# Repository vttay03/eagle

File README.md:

eagle
=====

misc. eagle pcb projects

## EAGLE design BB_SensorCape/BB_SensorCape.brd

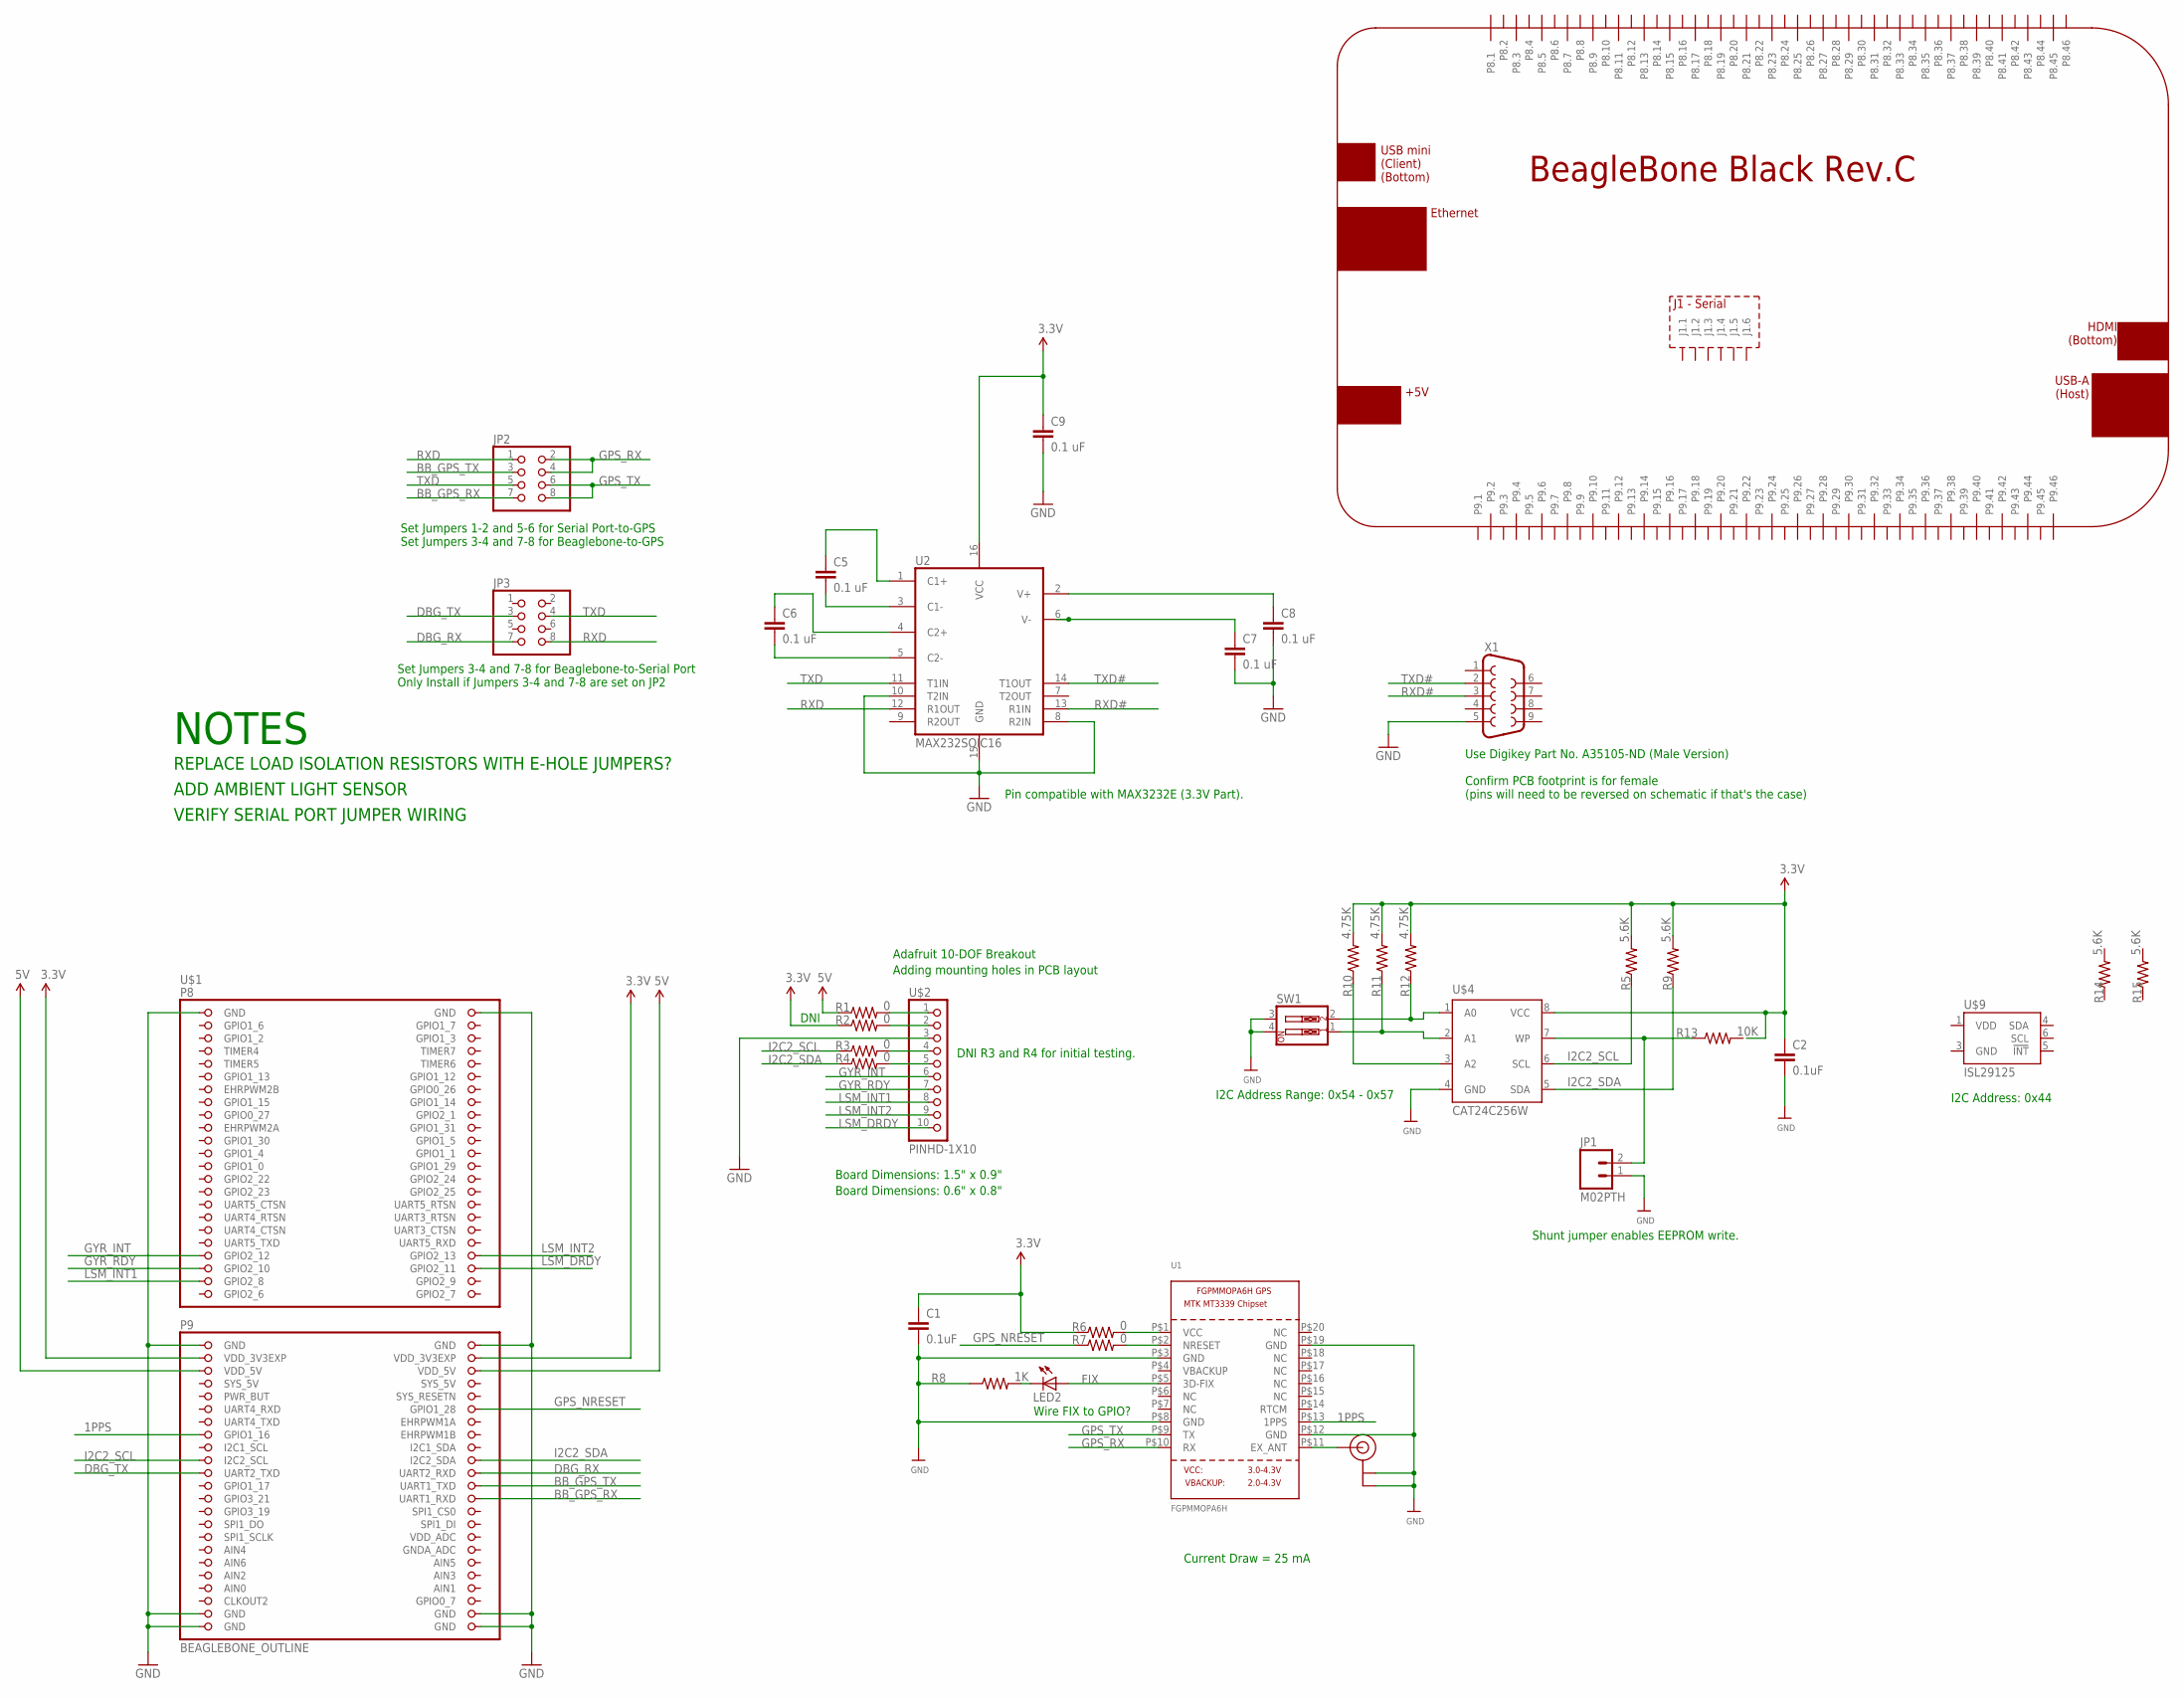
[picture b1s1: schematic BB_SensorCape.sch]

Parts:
C1, C2: 0.1uF; 0603-CAP
C5, C6, C7, C8, C9: 0.1 uF; 0805
JP1: M02PTH; 1X02
JP2, JP3: PINHD-2X4; 2X04
LED2: LEDCHIPLED_0805; CHIPLED_0805
PCB1: BEAGLEBONE_BLACK
R1, R2, R3, R4, R6, R7: 0; R0603
R5, R9, R14, R15: 5.6K; R0603
R8: 1K; R0603
R10, R11, R12: 4.75K; R0603
R13: 10K; R0603
SW1: SW_DIP-2-SMT-HALFSIZE; DIPSWITCH-02-50MIL
U1: FGPMMOPA6H
U2: MAX232SOIC16; SO016
U$1: BEAGLEBONE_OUTLINE; BEAGLEBONE_SHIELD
U$2: PINHD-1X10; 1X10-BIG
U$4: CAT24C256W; SO08
U$9: ISL29125; ODFN-LD-6
U$20: U.FL
X1: DB9MALE; DB9_MALE

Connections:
1PPS: PCB1.P9.15, U1.P$13 (1PPS), U$1.61 (GPIO1_16)
3.3V: C1.1, C2.1, C9.1, PCB1.P9.3, PCB1.P9.4, R2.1, R5.2, R6.1, R9.2, R10.2, R11.2, R12.2, R14.2, R15.2, U2.16 (VCC), U$1.49 (VDD_3V3EXP), U$1.50 (VDD_3V3EXP), U$4.8 (VCC); also elsewhere on the board
5V: PCB1.P9.5, PCB1.P9.6, R1.1, U$1.51 (VDD_5V), U$1.52 (VDD_5V)
BB_GPS_RX: JP2.7, PCB1.P9.26, U$1.72 (UART1_RXD)
BB_GPS_TX: JP2.3, PCB1.P9.24, U$1.70 (UART1_TXD)
DBG_RX: JP3.7, PCB1.P9.22
DBG_TX: JP3.3, PCB1.P9.21
GND: C1.2, C2.2, C7.2, C8.2, C9.2, JP1.1, PCB1.P8.1, PCB1.P8.2, PCB1.P9.1, PCB1.P9.2, PCB1.P9.43, PCB1.P9.44, PCB1.P9.45, PCB1.P9.46, R8.1, SW1.3, SW1.4, U1.P$3 (GND), U1.P$8 (GND), U1.P$12 (GND), U1.P$19 (GND), U2.8 (R2IN), U2.10 (T2IN), U2.15 (GND), U$1.1 (GND), U$1.2 (GND), U$1.47 (GND), U$1.48 (GND), U$1.89 (GND), U$1.90 (GND), U$1.91 (GND), U$1.92 (GND), U$2.3, U$4.4 (GND), U$9.3 (GND), U$20.P$1 (GND), U$20.P$2 (GND), X1.5; also elsewhere on the board
GPS_FIX: LED2.A, PCB1.P8.45, U1.P$5 (3D-FIX)
GPS_NRESET: PCB1.P9.12, R7.1, U$1.58 (GPIO1_28)
GPS_RX: JP2.2, JP2.4, U1.P$10 (RX)
GPS_TX: JP2.6, JP2.8, U1.P$9 (TX)
GYR_INT: PCB1.P8.39, U$1.39 (GPIO2_12), U$2.6
GYR_RDY: PCB1.P8.41, U$1.41 (GPIO2_10), U$2.7
I2C2_SCL: PCB1.P9.19, R3.1, R5.1, U$1.65 (I2C2_SCL), U$4.6 (SCL)
I2C2_SDA: PCB1.P9.20, R4.1, R9.1, U$1.66 (I2C2_SDA), U$4.5 (SDA)
ISL29125_INT: PCB1.P8.44, U$9.5 (!INT); also elsewhere on the board
LSM_DRDY: PCB1.P8.42, U$1.42 (GPIO2_11), U$2.10
LSM_INT1: PCB1.P8.43, U$1.43 (GPIO2_8), U$2.8
LSM_INT2: PCB1.P8.40, U$1.40 (GPIO2_13), U$2.9
unnamed: R1.2, U$2.1
unnamed: R2.2, U$2.2
unnamed: R4.2, U$2.5
unnamed: R3.2, U$2.4
unnamed: LED2.C, R8.2
unnamed: R6.2, U1.P$1 (VCC)
unnamed: U1.P$11 (EX_ANT), U$20.P$3 (SIGNAL)
unnamed: R7.2, U1.P$2 (NRESET)
unnamed: R12.1, SW1.2, U$4.1 (A0)
unnamed: C7.1, U2.6 (V-)
unnamed: R11.1, SW1.1, U$4.2 (A1)
unnamed: R10.1, U$4.3 (A2)
unnamed: JP1.2, R13.1, U$4.7 (WP)
unnamed: C5.2, U2.3 (C1-)
unnamed: R14.1, U$9.4 (SDA)
unnamed: R15.1, U$9.6 (SCL)
unnamed 36: U$9.1 (VDD); also elsewhere on the board
unnamed: C8.1, U2.2 (V+)
unnamed: C5.1, U2.1 (C1+)
unnamed: C6.1, U2.4 (C2+)
unnamed: C6.2, U2.5 (C2-)
RXD: JP2.1, JP3.8, U2.12 (R1OUT)
RXD#: U2.13 (R1IN), X1.3
TXD: JP2.5, JP3.4, U2.11 (T1IN)
TXD#: U2.14 (T1OUT), X1.2

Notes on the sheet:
DNI
Adafruit 10-DOF Breakout
Adding mounting holes in PCB layout
DNI R3 and R4 for initial testing.
Current Draw = 25 mA
Wire FIX to GPIO?
REPLACE LOAD ISOLATION RESISTORS WITH E-HOLE JUMPERS?
NOTES
ADD AMBIENT LIGHT SENSOR
VERIFY SERIAL PORT JUMPER WIRING
Shunt jumper enables EEPROM write.
I2C Address Range: 0x54 - 0x57
Pin compatible with MAX3232E (3.3V Part).
Use Digikey Part No. A35105-ND (Male Version) Confirm PCB footprint is for female (pins will need to be reversed on schematic if that's the case)
Set Jumpers 1-2 and 5-6 for Serial Port-to-GPS Set Jumpers 3-4 and 7-8 for Beaglebone-to-GPS
Set Jumpers 3-4 and 7-8 for Beaglebone-to-Serial Port Only Install if Jumpers 3-4 and 7-8 are set on JP2
Board Dimensions: 1.5" x 0.9"
Board Dimensions: 0.6" x 0.8"
I2C Address: 0x44

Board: 2 copper layers, 39 parts (0 on the bottom side), 45 nets, no tracks yet.

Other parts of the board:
C3: 1uF; 0805
C4: 0.1uF; 0603-CAP
R16: 10K; R0603
R17: 100; R0603

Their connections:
3.3V: R16.2, R17.2; also elsewhere on the board
GND: C3.2, C4.2; also elsewhere on the board
ISL29125_INT: R16.1; also elsewhere on the board
unnamed 36: C3.1, C4.1, R17.1; also elsewhere on the board

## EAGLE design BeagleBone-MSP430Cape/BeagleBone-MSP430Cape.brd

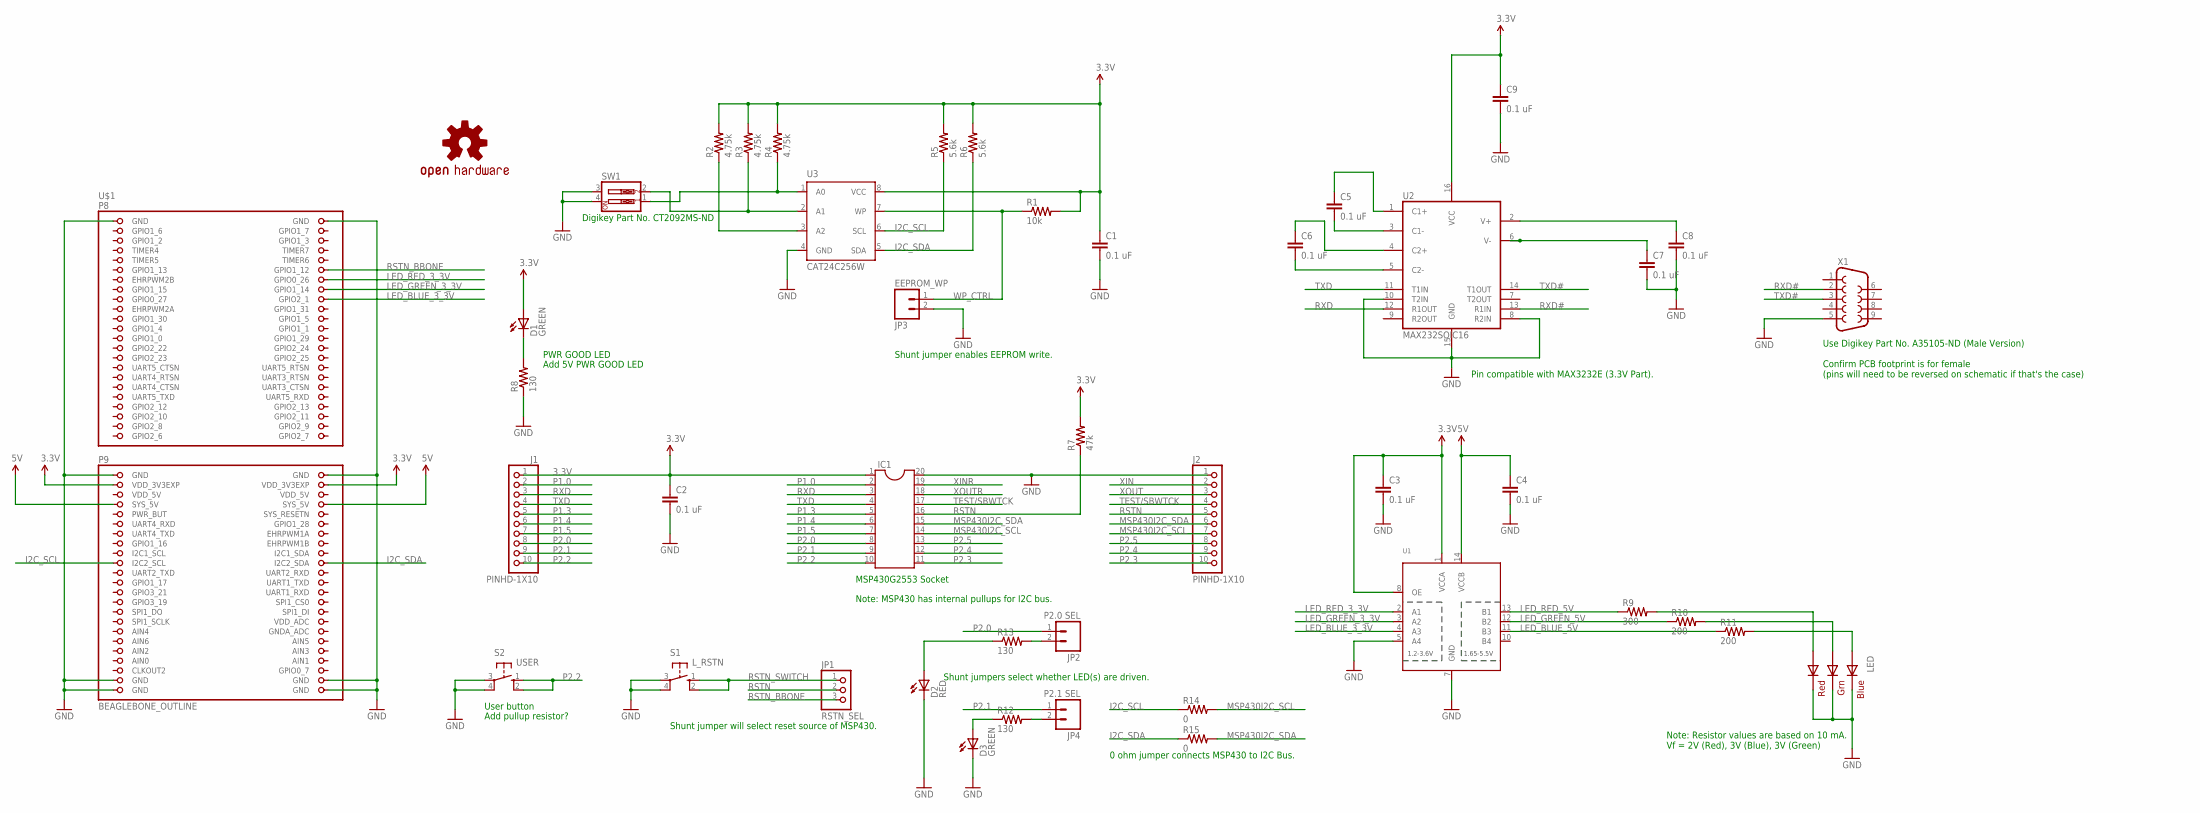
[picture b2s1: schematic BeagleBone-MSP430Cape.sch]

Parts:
C1, C2, C3, C4, C5, C6, C7, C8, C9: 0.1 uF; 0805
D1, D3: GREEN; LED-0603
D2: RED; LED-0603
IC1: DIL20S; SOCKET-20
J1, J2: PINHD-1X10; 1X10-BIG
JP1: RSTN_SEL; 1X03
JP2: P2.0 SEL; 1X02
JP3: EEPROM_WP; 1X02
JP4: P2.1 SEL; 1X02
LED: RGBLED5050
LOGO1: OSHW-LOGOL; OSHW-LOGO-L
R1: 10k; 0805
R2, R3, R4: 4.75k; 0805
R5, R6: 5.6k; 0805
R7: 47k; 0805
R8, R12, R13: 130; 0805
R9: 300; 0805
R10, R11: 200; 0805
R14, R15: 0; 0805
S1: L_RSTN; B3F-10XX
S2: USER; B3F-10XX
SW1: SW_DIP-2; DIPSWITCH-02
U1: TXB0104PWRSOIC14; SO14
U2: MAX232SOIC16; SO016
U3: CAT24C256W; SO08
U$1: BEAGLEBONE_OUTLINE; BEAGLEBONE_SHIELD
X1: DB9MALE; DB9_MALE

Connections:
3.3V: C1.1, C2.1, C3.1, C9.1, D1.A, IC1.1, J1.1, R1.2, R2.2, R3.2, R4.2, R5.2, R6.2, R7.2, U1.1 (VCCA), U1.8 (OE), U2.16 (VCC), U3.8 (VCC), U$1.49 (VDD_3V3EXP), U$1.50 (VDD_3V3EXP)
5V: C4.1, U1.14 (VCCB), U$1.53 (SYS_5V), U$1.54 (SYS_5V)
AIN0: U$1.85 (AIN0)
GND: C1.2, C2.2, C3.2, C4.2, C7.2, C8.2, C9.2, D2.C, D3.C, IC1.20, J2.1, JP3.2, LED.4 (BLUE_C), LED.5 (RED_C), LED.6 (GREEN_C), R8.1, S1.3, S1.4 (P1), S2.3, S2.4 (P1), SW1.3, SW1.4, U1.5 (A4), U1.7 (GND), U2.8 (R2IN), U2.10 (T2IN), U2.15 (GND), U3.4 (GND), U$1.1 (GND), U$1.2 (GND), U$1.47 (GND), U$1.48 (GND), U$1.89 (GND), U$1.90 (GND), U$1.91 (GND), U$1.92 (GND), X1.5
I2C_SCL: R5.1, R14.1, U3.6 (SCL), U$1.65 (I2C2_SCL)
I2C_SDA: R6.1, R15.1, U3.5 (SDA), U$1.66 (I2C2_SDA)
LED_BLUE_3_3V: U1.4 (A3), U$1.18 (GPIO2_1)
LED_BLUE_5V: R11.1, U1.11 (B3)
LED_GREEN_3_3V: U1.3 (A2), U$1.16 (GPIO1_14)
LED_GREEN_5V: R10.1, U1.12 (B2)
LED_RED_3_3V: U1.2 (A1), U$1.14 (GPIO0_26)
LED_RED_5V: R9.1, U1.13 (B1)
MSP430I2C_SCL: IC1.14, J2.7, R14.2
MSP430I2C_SDA: IC1.15, J2.6, R15.2
unnamed: C5.2, U2.3 (C1-)
unnamed: C7.1, U2.6 (V-)
unnamed: R2.1, U3.3 (A2)
unnamed: R3.1, SW1.2, U3.2 (A1)
unnamed: R4.1, SW1.1, U3.1 (A0)
unnamed: D2.A, R13.1
unnamed: JP2.2, R13.2
unnamed: JP4.2, R12.2
unnamed: D3.A, R12.1
unnamed: D1.C, R8.2
unnamed: LED.2 (RED_A), R9.2
unnamed: LED.1 (GREEN_A), R10.2
unnamed: LED.3 (BLUE_A), R11.2
unnamed: C8.1, U2.2 (V+)
unnamed: C5.1, U2.1 (C1+)
unnamed: C6.1, U2.4 (C2+)
unnamed: C6.2, U2.5 (C2-)
P1.0: IC1.2, J1.2
P1.3: IC1.5, J1.5
P1.4: IC1.6, J1.6
P1.5: IC1.7, J1.7
P2.0: IC1.8, J1.8, JP2.1
P2.1: IC1.9, J1.9, JP4.1
P2.2: IC1.10, J1.10, S2.1 (S), S2.2 (S1)
P2.3: IC1.11, J2.10
P2.4: IC1.12, J2.9
P2.5: IC1.13, J2.8
RSTN: IC1.16, J2.5, JP1.2, R7.1
RSTN_BBONE: JP1.3, U$1.12 (GPIO1_12)
RSTN_SWITCH: JP1.1, S1.1 (S), S1.2 (S1)
RXD: IC1.3, J1.3, U2.12 (R1OUT)
RXD#: U2.13 (R1IN), X1.2
TEST/SBWTCK: IC1.17, J2.4
TXD: IC1.4, J1.4, U2.11 (T1IN)
TXD#: U2.14 (T1OUT), X1.3
VDD_5V: U$1.51 (VDD_5V), U$1.52 (VDD_5V)
WP_CTRL: JP3.1, R1.1, U3.7 (WP)
XIN: J2.2
XINR: IC1.19
XOUT: J2.3
XOUTR: IC1.18

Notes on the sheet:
Digikey Part No. CT2092MS-ND
MSP430G2553 Socket
Note: MSP430 has internal pullups for I2C bus.
Note: Resistor values are based on 10 mA. Vf = 2V (Red), 3V (Blue), 3V (Green)
Shunt jumper will select reset source of MSP430.
Shunt jumper enables EEPROM write.
Pin compatible with MAX3232E (3.3V Part).
Use Digikey Part No. A35105-ND (Male Version) Confirm PCB footprint is for female (pins will need to be reversed on schematic if that's the case)
User button
Shunt jumpers select whether LED(s) are driven.
0 ohm jumper connects MSP430 to I2C Bus.
Add pullup resistor?
PWR GOOD LED
Add 5V PWR GOOD LED

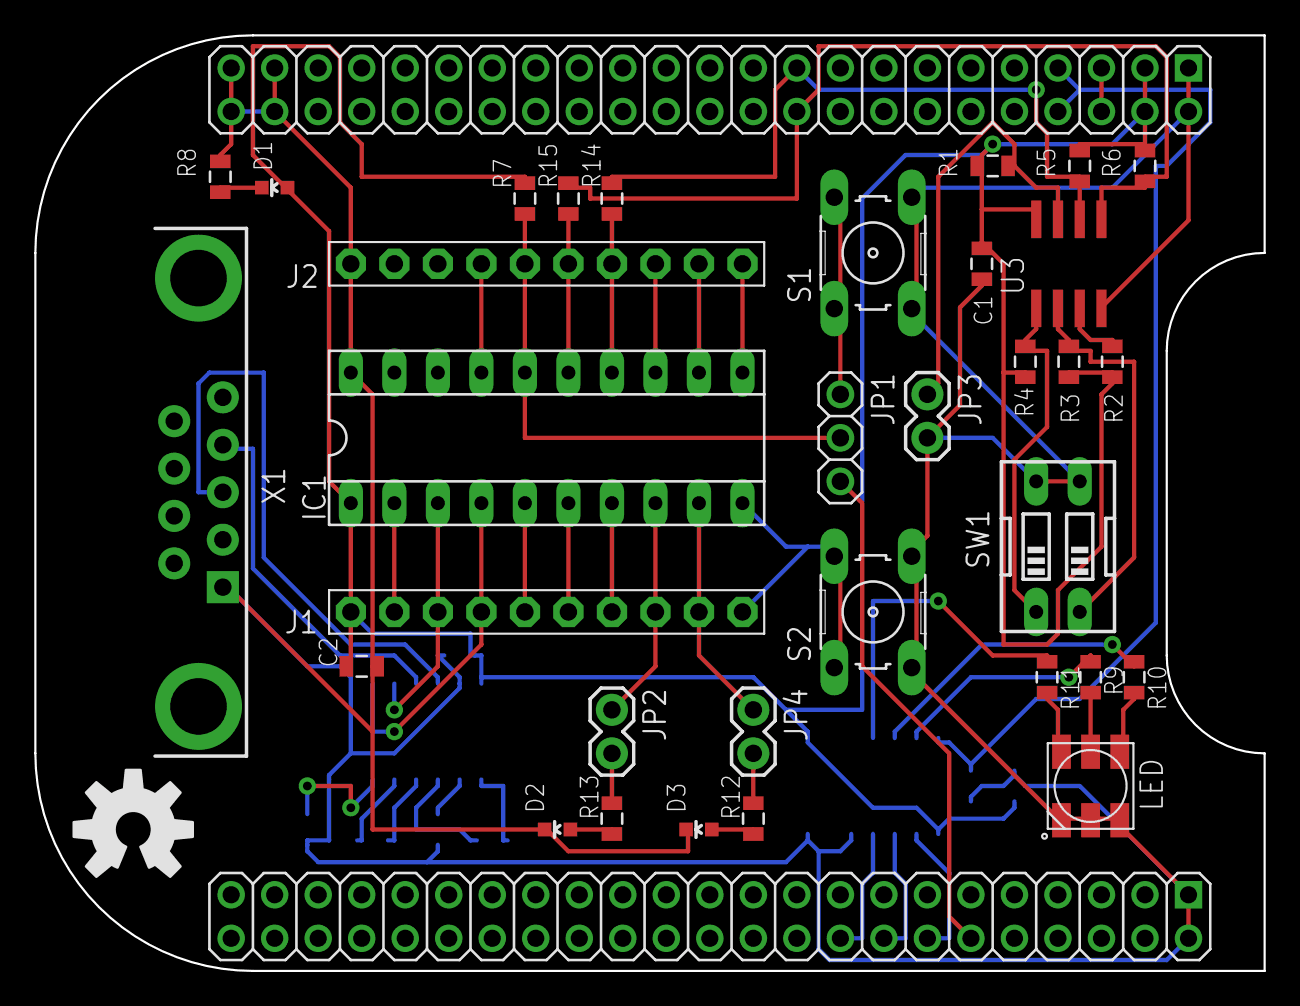
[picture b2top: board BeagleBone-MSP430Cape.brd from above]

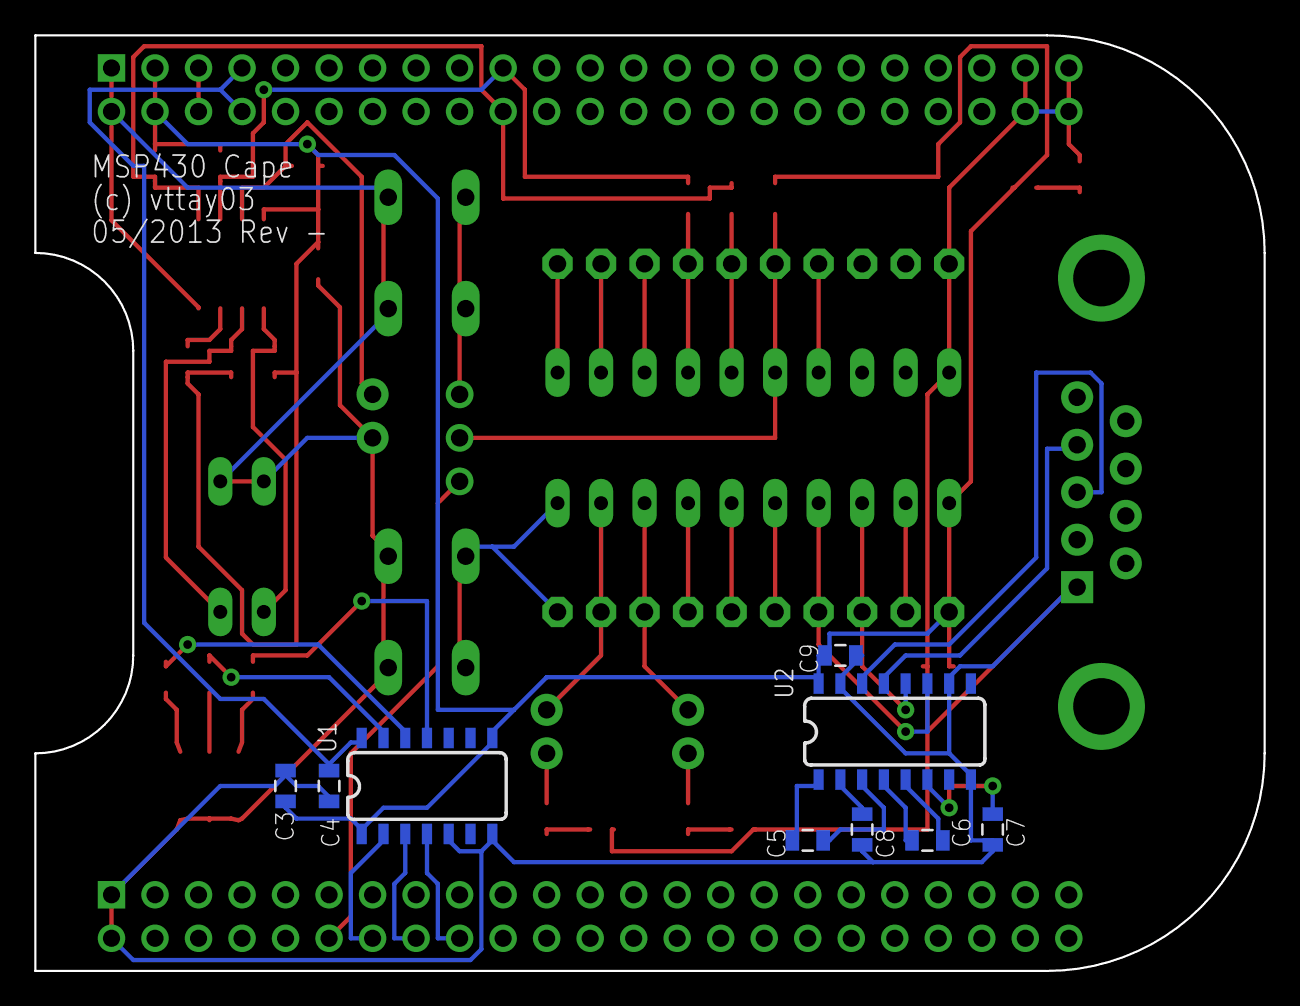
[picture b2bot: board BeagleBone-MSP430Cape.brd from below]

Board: 2 copper layers, 71.8 x 54.6 mm, 44 parts (9 on the bottom side), 50 nets.

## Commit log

2013-05-08 schematic updates 05/07
2013-05-09 library updates for EEPROM part
2013-05-11 updates 05/10/13
2013-05-12 changes 05/12/13
2013-05-14 schematic/board updates 05/13
2014-12-11 schematic updates 12/10
2014-12-24 schematic updates 12/23
2014-12-25 updates 12/24
    added ISL29125 and started PWB design for area study
2015-01-03 Schematic/Board updates 01/03
    Minor updates over holiday break
2015-01-04 Board updates 01/04
    routing at ~98%
2015-02-03 Schematic changes 02/03
    Moved to FTDI interface for serial console
    Refined jumper selection for serial console
    Using TSL2561 BoB for ambient light sensor

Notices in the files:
parts and their libraries:
SparkFun-Capacitors: Licensing: Creative Commons ShareAlike 4.0 International - https://creativecommons.org/licenses/by-sa/4.0
SparkFun-DigitalIC: Licensing: CC v3.0 Share-Alike You are welcome to use this library for commercial purposes.
